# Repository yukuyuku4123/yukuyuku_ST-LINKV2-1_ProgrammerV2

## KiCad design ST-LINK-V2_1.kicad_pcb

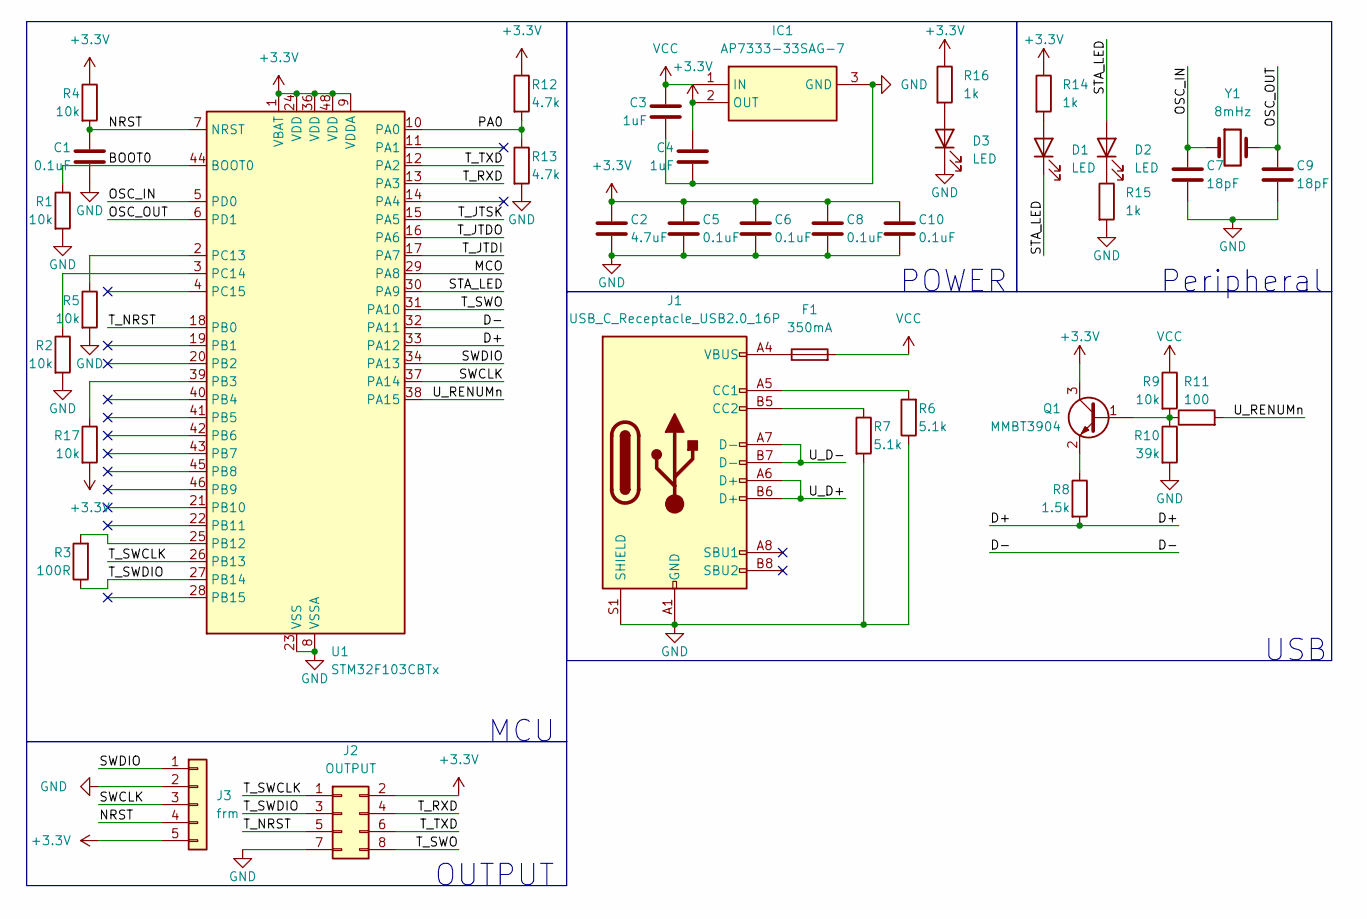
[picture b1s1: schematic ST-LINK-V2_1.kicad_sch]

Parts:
C1, C5, C6, C8, C10: 0.1uF; C_0402_1005Metric
C2: 4.7uF; C_0603_1608Metric
C3, C4: 1uF; C_0603_1608Metric
C7, C9: 18pF; C_0402_1005Metric
D1, D2, D3: LED; LED_0603_1608Metric
F1: 350mA; Fuse_0603_1608Metric
IC1: AP7333-33SAG-7; SOT96P240X135-3N; Mouser Part Number 621-AP7333-33SAG-7
J1: USB_C_Receptacle_USB2.0_16P; USB_C_Receptacle_GCT_USB4105-xx-A_16P_TopMnt_Horizontal
J2: OUTPUT; PinHeader_2x04_P2.54mm_Vertical
J3: frm; PinHeader_1x05_P2.54mm_Vertical
Q1: MMBT3904; SOT-23
R1, R2, R4, R5, R9, R17: 10k; R_0603_1608Metric
R3: 100R; R_0603_1608Metric
R6, R7: 5.1k; R_0603_1608Metric
R8: 1.5k; R_0603_1608Metric
R10: 39k; R_0603_1608Metric
R11: 100; R_0603_1608Metric
R12, R13: 4.7k; R_0603_1608Metric
R14, R15, R16: 1k; R_0603_1608Metric
U1: STM32F103CBTx; LQFP-48_7x7mm_P0.5mm
Y1: 8mHz; Crystal_HC49-4H_Vertical

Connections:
+3.3V: C2.1, C4.1, C5.1, C6.1, C8.1, C10.1, IC1.2 (OUT), J2.2, J3.5, Q1.3 (C), R4.1, R12.1, R14.1, R16.1, R17.2, U1.1 (VBAT), U1.9 (VDDA), U1.24 (VDD), U1.36 (VDD), U1.48 (VDD)
/BOOT0: R1.1, U1.44 (BOOT0)
/D+: R8.2, U1.33 (PA12)
/D-: U1.32 (PA11)
/MCO: U1.29 (PA8)
/NRST: C1.1, J3.4, R4.2, U1.7 (NRST)
/OSC_IN: C7.1, U1.5 (PD0), Y1.1
/OSC_OUT: C9.1, U1.6 (PD1), Y1.2
/PA0: R12.2, R13.1, U1.10 (PA0)
/STA_LED: D1.1 (K), D2.2 (A), U1.30 (PA9)
/SWCLK: J3.3, U1.37 (PA14)
/SWDIO: J3.1, U1.34 (PA13)
/T_JTDI: U1.17 (PA7)
/T_JTDO: U1.16 (PA6)
/T_JTSK: U1.15 (PA5)
/T_NRST: J2.5, U1.18 (PB0)
/T_RXD: J2.4, U1.13 (PA3)
/T_SWCLK: J2.1, U1.26 (PB13)
/T_SWDIO: J2.3, R3.1, U1.27 (PB14)
/T_SWO: J2.8, U1.31 (PA10)
/T_TXD: J2.6, U1.12 (PA2)
/U_D+: J1.A6 (D+), J1.B6 (D+)
/U_D-: J1.A7 (D-), J1.B7 (D-)
/U_RENUMn: R11.2, U1.38 (PA15)
GND: C1.2, C2.2, C3.2, C4.2, C5.2, C6.2, C7.2, C8.2, C9.2, C10.2, D3.1 (K), IC1.3 (GND), J1.A1 (GND), J1.A12 (GND), J1.B1 (GND), J1.B12 (GND), J1.S1 (SHIELD), J2.7, J3.2, R1.2, R2.2, R5.2, R6.1, R7.2, R10.2, R13.2, R15.2, U1.8 (VSSA), U1.23 (VSS), U1.35 (VSS), U1.47 (VSS)
unnamed: D1.2 (A), R14.2
unnamed: D2.1 (K), R15.1
unnamed: D3.2 (A), R16.2
unnamed: F1.1, J1.A4 (VBUS), J1.A9 (VBUS), J1.B4 (VBUS), J1.B9 (VBUS)
unnamed: J1.A5 (CC1), R6.2
unnamed: J1.B5 (CC2), R7.1
unnamed: Q1.1 (B), R9.2, R10.1, R11.1
unnamed: Q1.2 (E), R8.1
unnamed: R17.1, U1.39 (PB3)
unnamed: R3.2, U1.25 (PB12)
unnamed: R5.1, U1.2 (PC13)
unnamed: R2.1, U1.3 (PC14)
VCC: C3.1, F1.2, IC1.1 (IN), R9.1

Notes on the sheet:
Peripheral
OUTPUT
POWER
USB
MCU

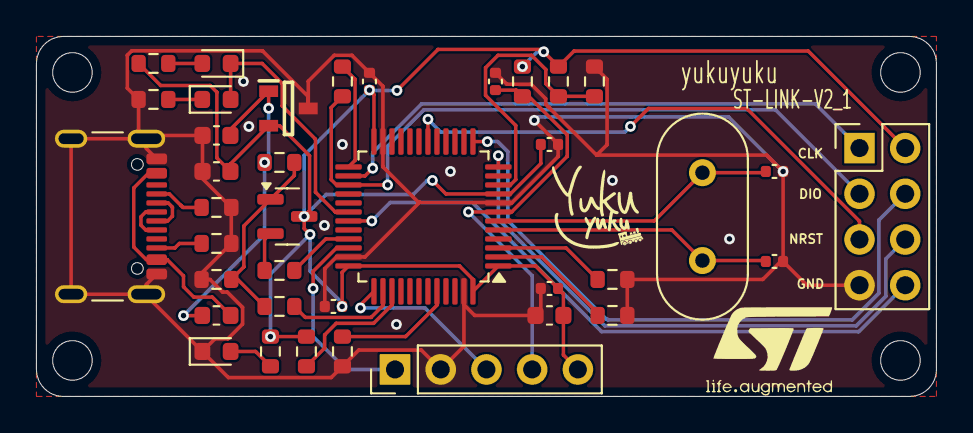
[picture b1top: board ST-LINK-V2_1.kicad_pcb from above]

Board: 2 copper layers, 50.0 x 20.0 mm, 38 parts (0 on the bottom side), 33 nets.

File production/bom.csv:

Designator,Footprint,Quantity,Value,LCSC Part #
"C1, C10, C5, C6, C8",0402,5,0.1uF,
C2,0603,1,4.7uF,
"C3, C4",0603,2,1uF,
"C7, C9",0402,2,18pF,
"D1, D2, D3",0603,3,LED,
F1,0603,1,350mA,
IC1,SOT96P240X135-3N,1,AP7333-33SAG-7,
J1,USB_C_Receptacle_GCT_USB4105-xx-A_16P_TopMnt_Horizontal,1,USB_C_Receptacle_USB2.0_16P,
J2,PinHeader_2x04_P2.54mm_Vertical,1,OUTPUT,
J3,PinHeader_1x05_P2.54mm_Vertical,1,frm,
Q1,SOT-23,1,MMBT3904,
"R1, R17, R2, R4, R5, R9",0603,6,10k,
R10,0603,1,39k,
R11,0603,1,100,
"R12, R13",0603,2,4.7k,
"R14, R15, R16",0603,3,1k,
R3,0603,1,100R,
"R6, R7",0603,2,5.1k,
R8,0603,1,1.5k,
U1,LQFP-48_7x7mm_P0.5mm,1,STM32F103CBTx,
Y1,Crystal_HC49-4H_Vertical,1,8mHz,

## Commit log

2024-08-02 Ver-1.0
2024-10-29 Ver-1.1
